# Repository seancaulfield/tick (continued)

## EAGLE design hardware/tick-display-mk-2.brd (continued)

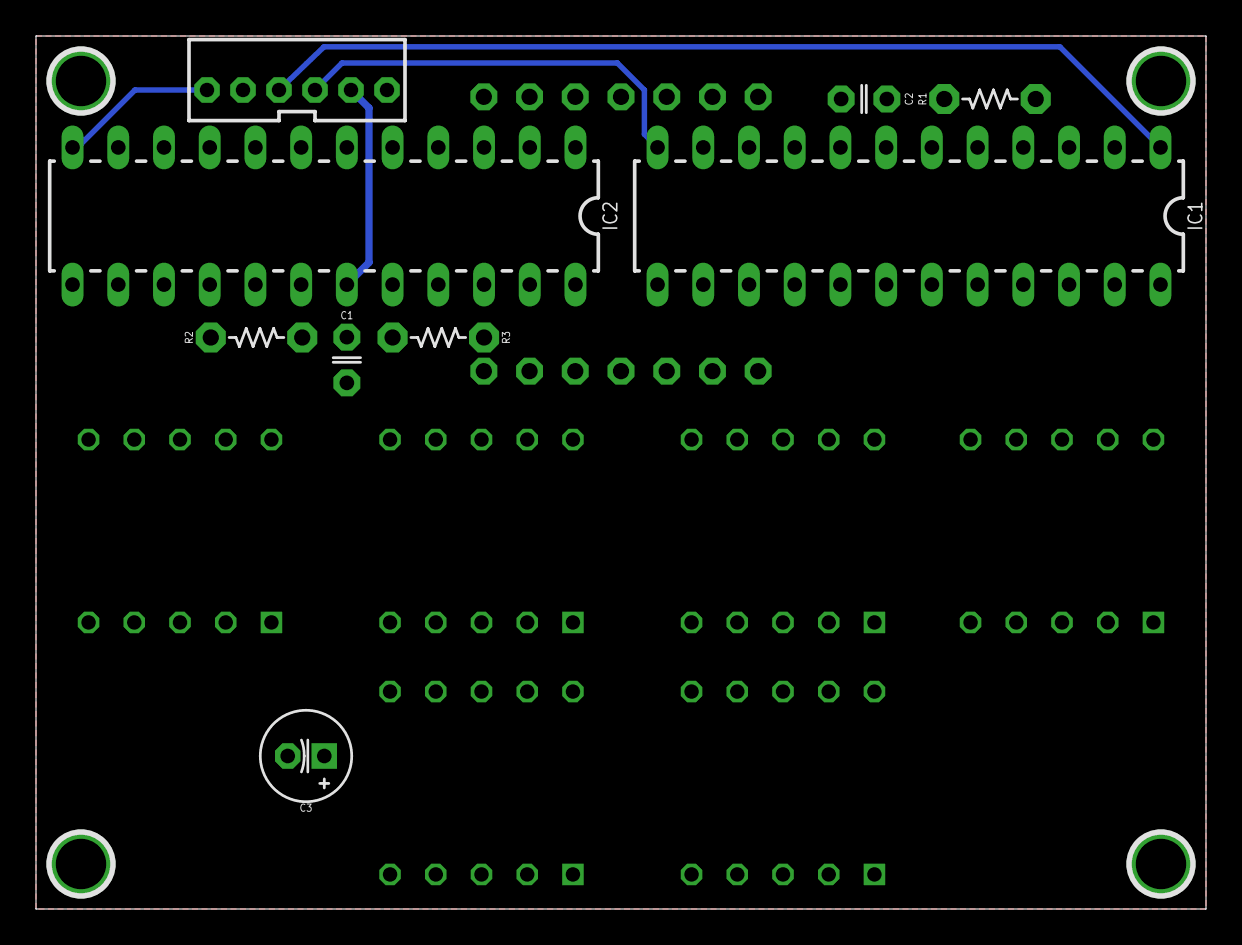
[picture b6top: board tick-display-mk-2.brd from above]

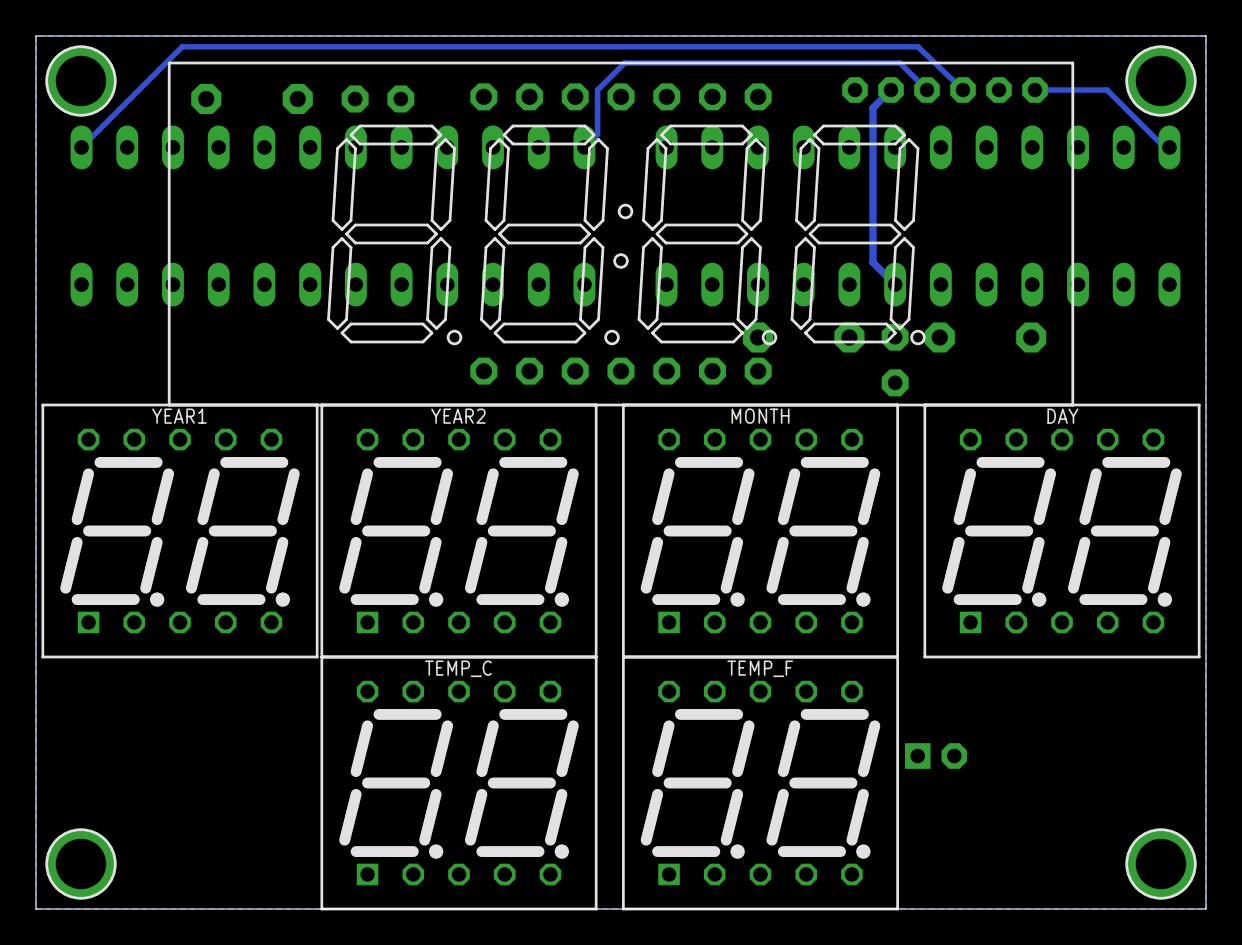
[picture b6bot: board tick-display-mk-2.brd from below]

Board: 2 copper layers, 65.0 x 48.5 mm, 20 parts (7 on the bottom side), 40 nets.
